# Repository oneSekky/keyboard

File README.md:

# keyboard
Custom keyboard for a couch TV setup. Screen build into the board, custom buttons, dials, and a trackball mouse.

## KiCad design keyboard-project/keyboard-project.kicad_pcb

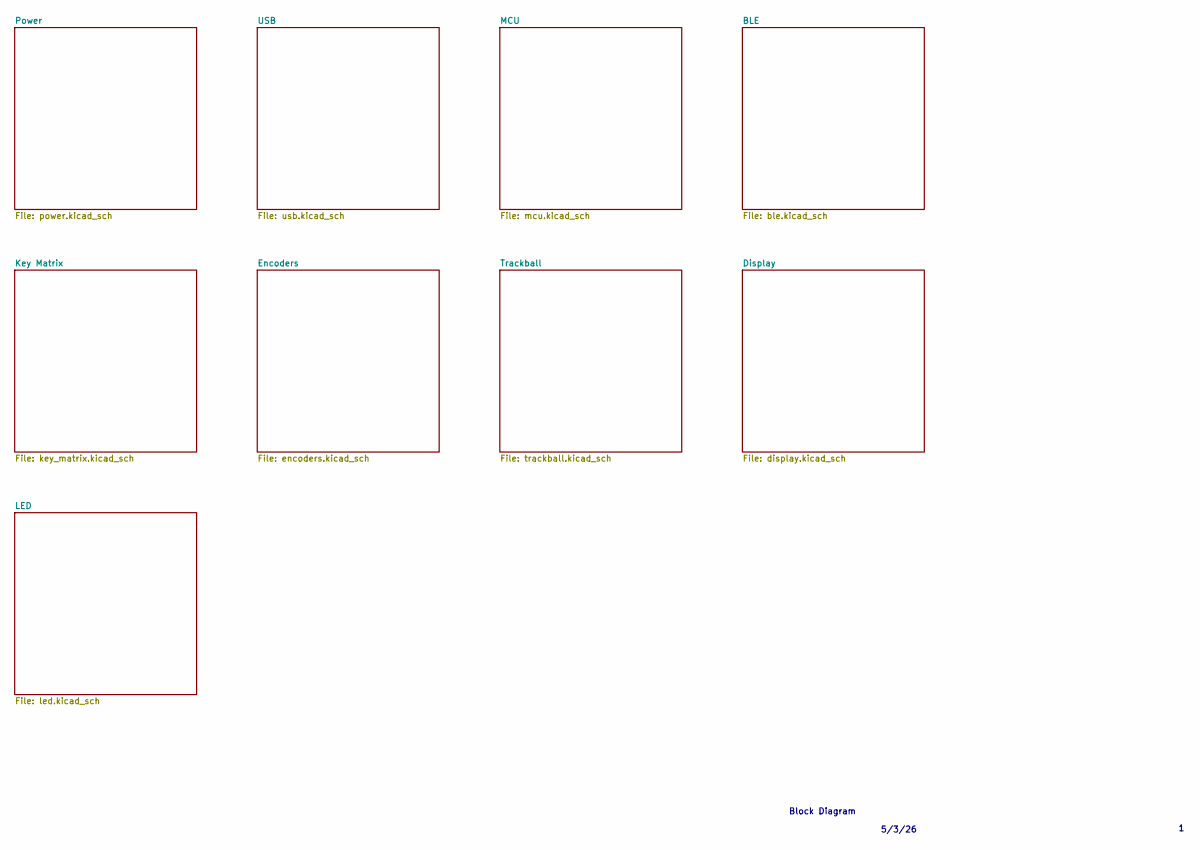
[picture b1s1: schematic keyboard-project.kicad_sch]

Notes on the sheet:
5/3/26
Block Diagram

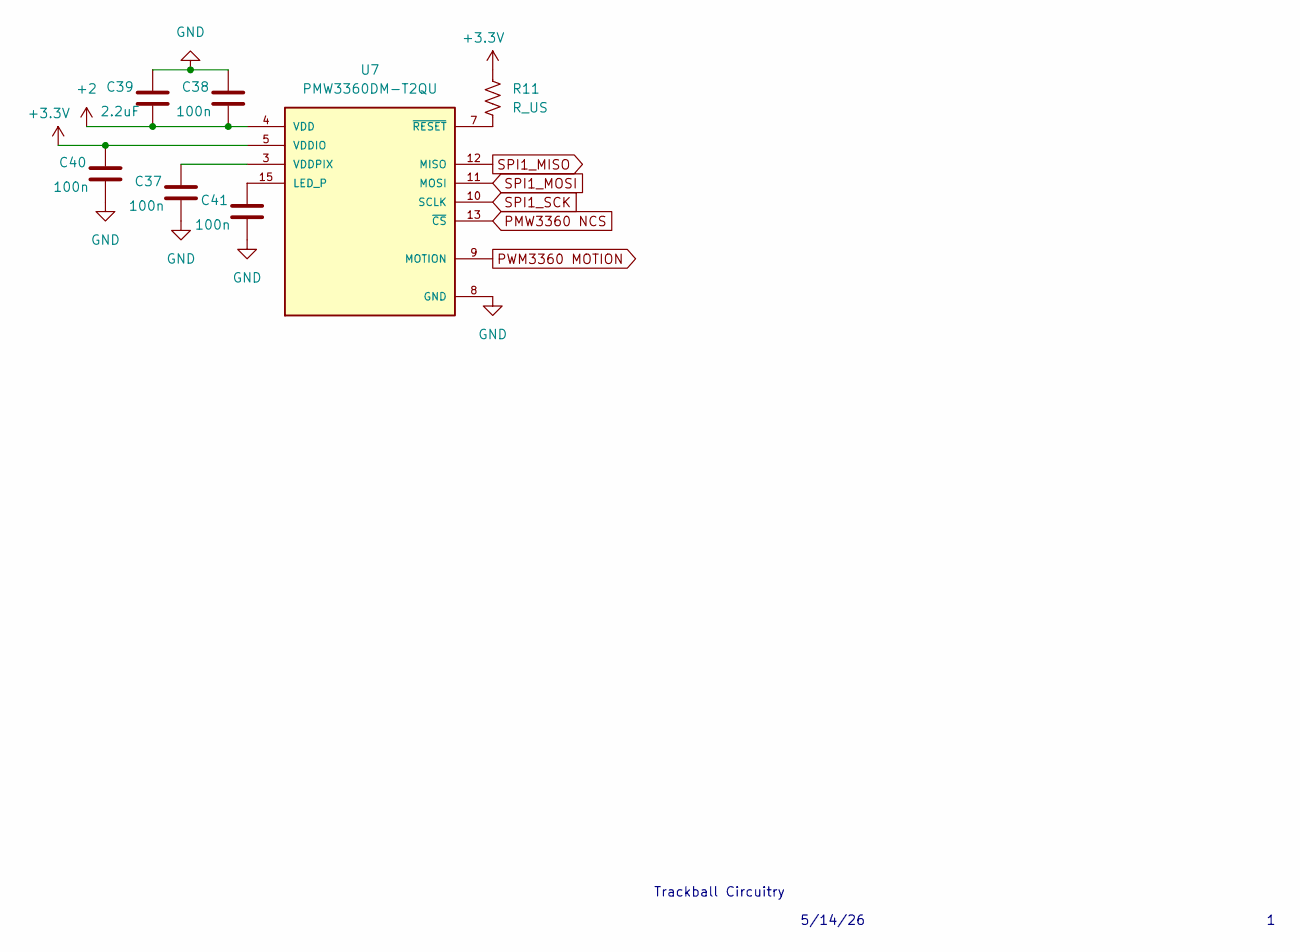
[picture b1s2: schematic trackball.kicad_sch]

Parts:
C37, C38, C40, C41: 100n; C_1206_3216Metric_Pad1.33x1.80mm_HandSolder
C39: 2.2uF; C_1206_3216Metric_Pad1.33x1.80mm_HandSolder
R11: R_US; R_1206_3216Metric_Pad1.30x1.75mm_HandSolder
U7: PMW3360DM-T2QU; PMW3360; MANUFACTURER_PART_NUMBER PMW3360DM-T2QU

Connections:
+2: C38.2, C39.2, U7.4 (VDD); also elsewhere on the board
+3.3V: C40.1, R11.1, U7.5 (VDDIO); also elsewhere on the board
GND: C37.2, C38.1, C39.1, C40.2, C41.2, U7.8 (GND); also elsewhere on the board
unnamed: C41.1, U7.15 (LED_P)
unnamed: C37.1, U7.3 (VDDPIX)
unnamed: R11.2, U7.7 (~RESET)
PMW3360 NCS: U7.13 (~CS); also elsewhere on the board
PWM3360 MOTION: U7.9 (MOTION); also elsewhere on the board
SPI1_MISO: U7.12 (MISO); also elsewhere on the board
SPI1_MOSI: U7.11 (MOSI); also elsewhere on the board
SPI1_SCK: U7.10 (SCLK); also elsewhere on the board

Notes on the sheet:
5/14/26
Trackball Circuitry

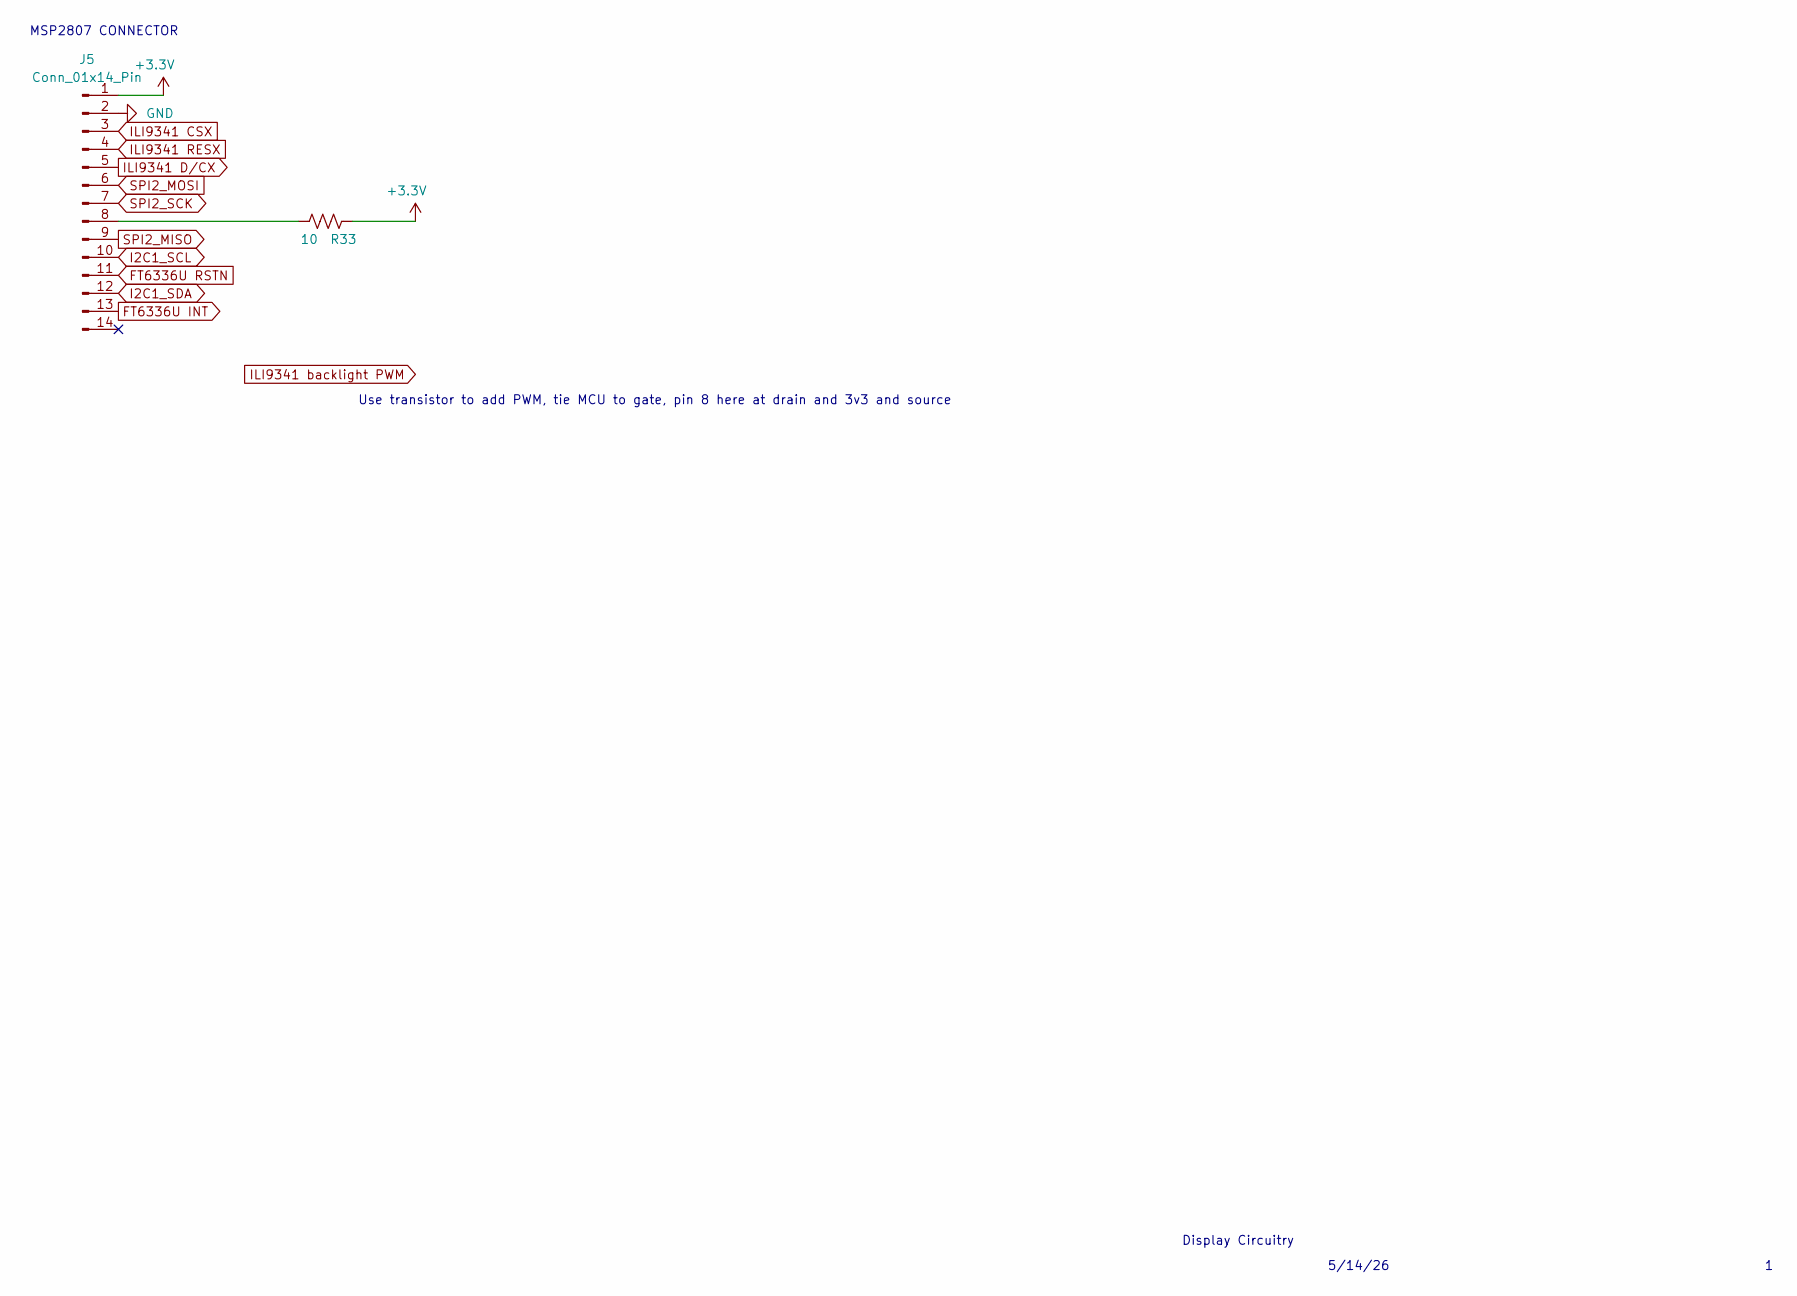
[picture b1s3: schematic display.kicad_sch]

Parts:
J5: Conn_01x14_Pin; PinHeader_1x14_P1.00mm_Vertical
R33: 10; R_1206_3216Metric_Pad1.30x1.75mm_HandSolder

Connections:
+3.3V: J5.1, R33.2; also elsewhere on the board
FT6336U INT: J5.13; also elsewhere on the board
FT6336U RSTN: J5.11; also elsewhere on the board
GND: J5.2; also elsewhere on the board
I2C1_SCL: J5.10; also elsewhere on the board
I2C1_SDA: J5.12; also elsewhere on the board
ILI9341 CSX: J5.3; also elsewhere on the board
ILI9341 D/CX: J5.5; also elsewhere on the board
ILI9341 RESX: J5.4; also elsewhere on the board
unnamed: J5.8, R33.1
SPI2_MISO: J5.9; also elsewhere on the board
SPI2_MOSI: J5.6; also elsewhere on the board
SPI2_SCK: J5.7; also elsewhere on the board

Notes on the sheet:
Display Circuitry
MSP2807 CONNECTOR
Use transistor to add PWM, tie MCU to gate, pin 8 here at drain and 3v3 and source
5/14/26

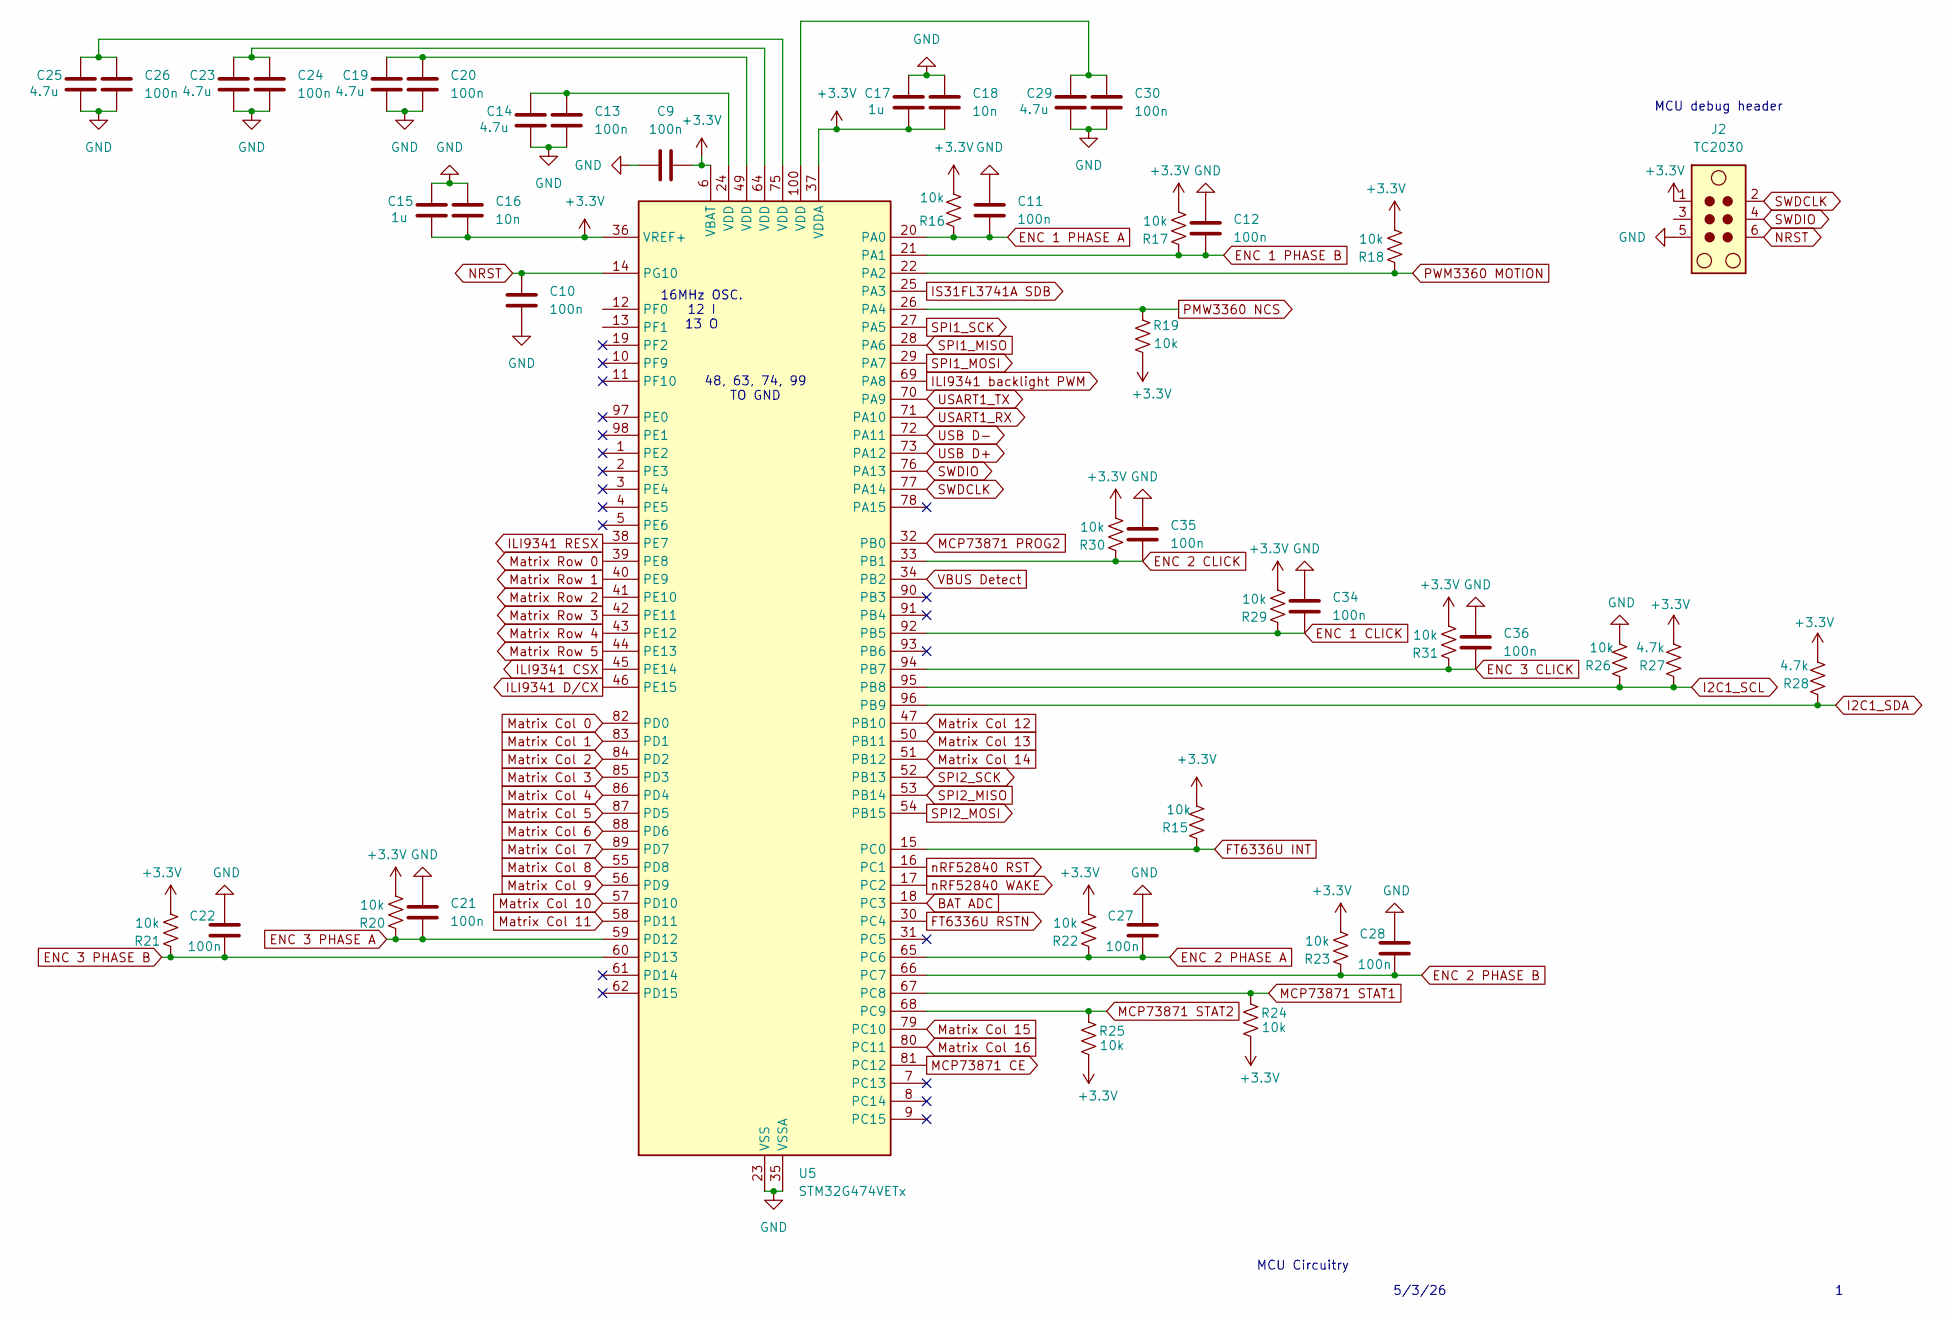
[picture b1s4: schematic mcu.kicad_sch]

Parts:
C9, C10, C11, C12, C13, C20, C21, C22, C24, C26, C27, C28, C30, C34, C35, C36: 100n; C_1206_3216Metric_Pad1.33x1.80mm_HandSolder
C14, C19, C23, C25, C29: 4.7u; C_1206_3216Metric_Pad1.33x1.80mm_HandSolder
C15, C17: 1u; C_1206_3216Metric_Pad1.33x1.80mm_HandSolder
C16, C18: 10n; C_1206_3216Metric_Pad1.33x1.80mm_HandSolder
J2: TC2030; Tag-Connect_TC2030-IDC-NL_2x03_P1.27mm_Vertical
R15, R16, R17, R18, R19, R20, R21, R22, R23, R24, R25, R26, R29, R30, R31: 10k; R_1206_3216Metric_Pad1.30x1.75mm_HandSolder
R27, R28: 4.7k; R_1206_3216Metric_Pad1.30x1.75mm_HandSolder
U5: STM32G474VETx; LQFP-100_14x14mm_P0.5mm

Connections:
+3.3V: C9.2, C15.2, C16.1, C17.2, C18.1, J2.1, R15.2, R16.2, R17.2, R18.2, R19.2, R20.2, R21.2, R22.2, R23.2, R24.2, R25.2, R27.2, R28.2, R29.2, R30.2, R31.2, U5.6 (VBAT), U5.36 (VREF+), U5.37 (VDDA); also elsewhere on the board
BAT ADC: U5.18 (PC3); also elsewhere on the board
ENC 1 CLICK: C34.1, R29.1, U5.92 (PB5); also elsewhere on the board
ENC 1 PHASE A: C11.1, R16.1, U5.20 (PA0); also elsewhere on the board
ENC 1 PHASE B: C12.1, R17.1, U5.21 (PA1); also elsewhere on the board
ENC 2 CLICK: C35.1, R30.1, U5.33 (PB1); also elsewhere on the board
ENC 2 PHASE A: C27.1, R22.1, U5.65 (PC6); also elsewhere on the board
ENC 2 PHASE B: C28.1, R23.1, U5.66 (PC7); also elsewhere on the board
ENC 3 CLICK: C36.1, R31.1, U5.94 (PB7); also elsewhere on the board
ENC 3 PHASE A: C21.1, R20.1, U5.59 (PD12); also elsewhere on the board
ENC 3 PHASE B: C22.1, R21.1, U5.60 (PD13); also elsewhere on the board
FT6336U INT: R15.1, U5.15 (PC0); also elsewhere on the board
FT6336U RSTN: U5.30 (PC4); also elsewhere on the board
GND: C9.1, C10.1, C11.2, C12.2, C13.1, C14.2, C15.1, C16.2, C17.1, C18.2, C19.2, C20.1, C21.2, C22.2, C23.2, C24.1, C25.2, C26.1, C27.2, C28.2, C29.2, C30.1, C34.2, C35.2, C36.2, J2.5, R26.2, U5.23 (VSS), U5.35 (VSSA), U5.48 (VSS), U5.63 (VSS), U5.74 (VSS), U5.99 (VSS); also elsewhere on the board
I2C1_SCL: R26.1, R27.1, U5.95 (PB8); also elsewhere on the board
I2C1_SDA: R28.1, U5.96 (PB9); also elsewhere on the board
ILI9341 CSX: U5.45 (PE14); also elsewhere on the board
ILI9341 D/CX: U5.46 (PE15); also elsewhere on the board
ILI9341 RESX: U5.38 (PE7); also elsewhere on the board
ILI9341 backlight PWM: U5.69 (PA8)
IS31FL3741A SDB: U5.25 (PA3); also elsewhere on the board
MCP73871 CE: U5.81 (PC12); also elsewhere on the board
MCP73871 PROG2: U5.32 (PB0); also elsewhere on the board
MCP73871 STAT1: R24.1, U5.67 (PC8); also elsewhere on the board
MCP73871 STAT2: R25.1, U5.68 (PC9); also elsewhere on the board
Matrix Col 0: U5.82 (PD0); also elsewhere on the board
Matrix Col 1: U5.83 (PD1); also elsewhere on the board
Matrix Col 2: U5.84 (PD2); also elsewhere on the board
Matrix Col 3: U5.85 (PD3); also elsewhere on the board
Matrix Col 4: U5.86 (PD4); also elsewhere on the board
Matrix Col 5: U5.87 (PD5); also elsewhere on the board
Matrix Col 6: U5.88 (PD6); also elsewhere on the board
Matrix Col 7: U5.89 (PD7); also elsewhere on the board
Matrix Col 8: U5.55 (PD8); also elsewhere on the board
Matrix Col 9: U5.56 (PD9); also elsewhere on the board
Matrix Col 10: U5.57 (PD10); also elsewhere on the board
Matrix Col 11: U5.58 (PD11); also elsewhere on the board
Matrix Col 12: U5.47 (PB10); also elsewhere on the board
Matrix Col 13: U5.50 (PB11); also elsewhere on the board
Matrix Col 14: U5.51 (PB12); also elsewhere on the board
Matrix Col 15: U5.79 (PC10); also elsewhere on the board
Matrix Col 16: U5.80 (PC11); also elsewhere on the board
Matrix Row 0: U5.39 (PE8); also elsewhere on the board
Matrix Row 1: U5.40 (PE9); also elsewhere on the board
Matrix Row 2: U5.41 (PE10); also elsewhere on the board
Matrix Row 3: U5.42 (PE11); also elsewhere on the board
Matrix Row 4: U5.43 (PE12); also elsewhere on the board
Matrix Row 5: U5.44 (PE13); also elsewhere on the board
NRST: C10.2, J2.6, U5.14 (PG10)
unnamed: C13.2, C14.1, U5.24 (VDD)
unnamed: C19.1, C20.2, U5.49 (VDD)
unnamed: C23.1, C24.2, U5.64 (VDD)
unnamed: C25.1, C26.2, U5.75 (VDD)
unnamed: C29.1, C30.2, U5.100 (VDD)
PMW3360 NCS: R19.1, U5.26 (PA4); also elsewhere on the board
PWM3360 MOTION: R18.1, U5.22 (PA2); also elsewhere on the board
SPI1_MISO: U5.28 (PA6); also elsewhere on the board
SPI1_MOSI: U5.29 (PA7); also elsewhere on the board
SPI1_SCK: U5.27 (PA5); also elsewhere on the board
SPI2_MISO: U5.53 (PB14); also elsewhere on the board
SPI2_MOSI: U5.54 (PB15); also elsewhere on the board
SPI2_SCK: U5.52 (PB13); also elsewhere on the board
SWDCLK: J2.2, U5.77 (PA14)
SWDIO: J2.4, U5.76 (PA13)
USART1_RX: U5.71 (PA10); also elsewhere on the board
USART1_TX: U5.70 (PA9); also elsewhere on the board
USB D+: U5.73 (PA12); also elsewhere on the board
USB D-: U5.72 (PA11); also elsewhere on the board
VBUS Detect: U5.34 (PB2); also elsewhere on the board
nRF52840 RST: U5.16 (PC1); also elsewhere on the board
nRF52840 WAKE: U5.17 (PC2); also elsewhere on the board

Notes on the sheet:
MCU Circuitry
MCU debug header
48, 63, 74, 99 TO GND
16MHz OSC. 12 I 13 O
5/3/26

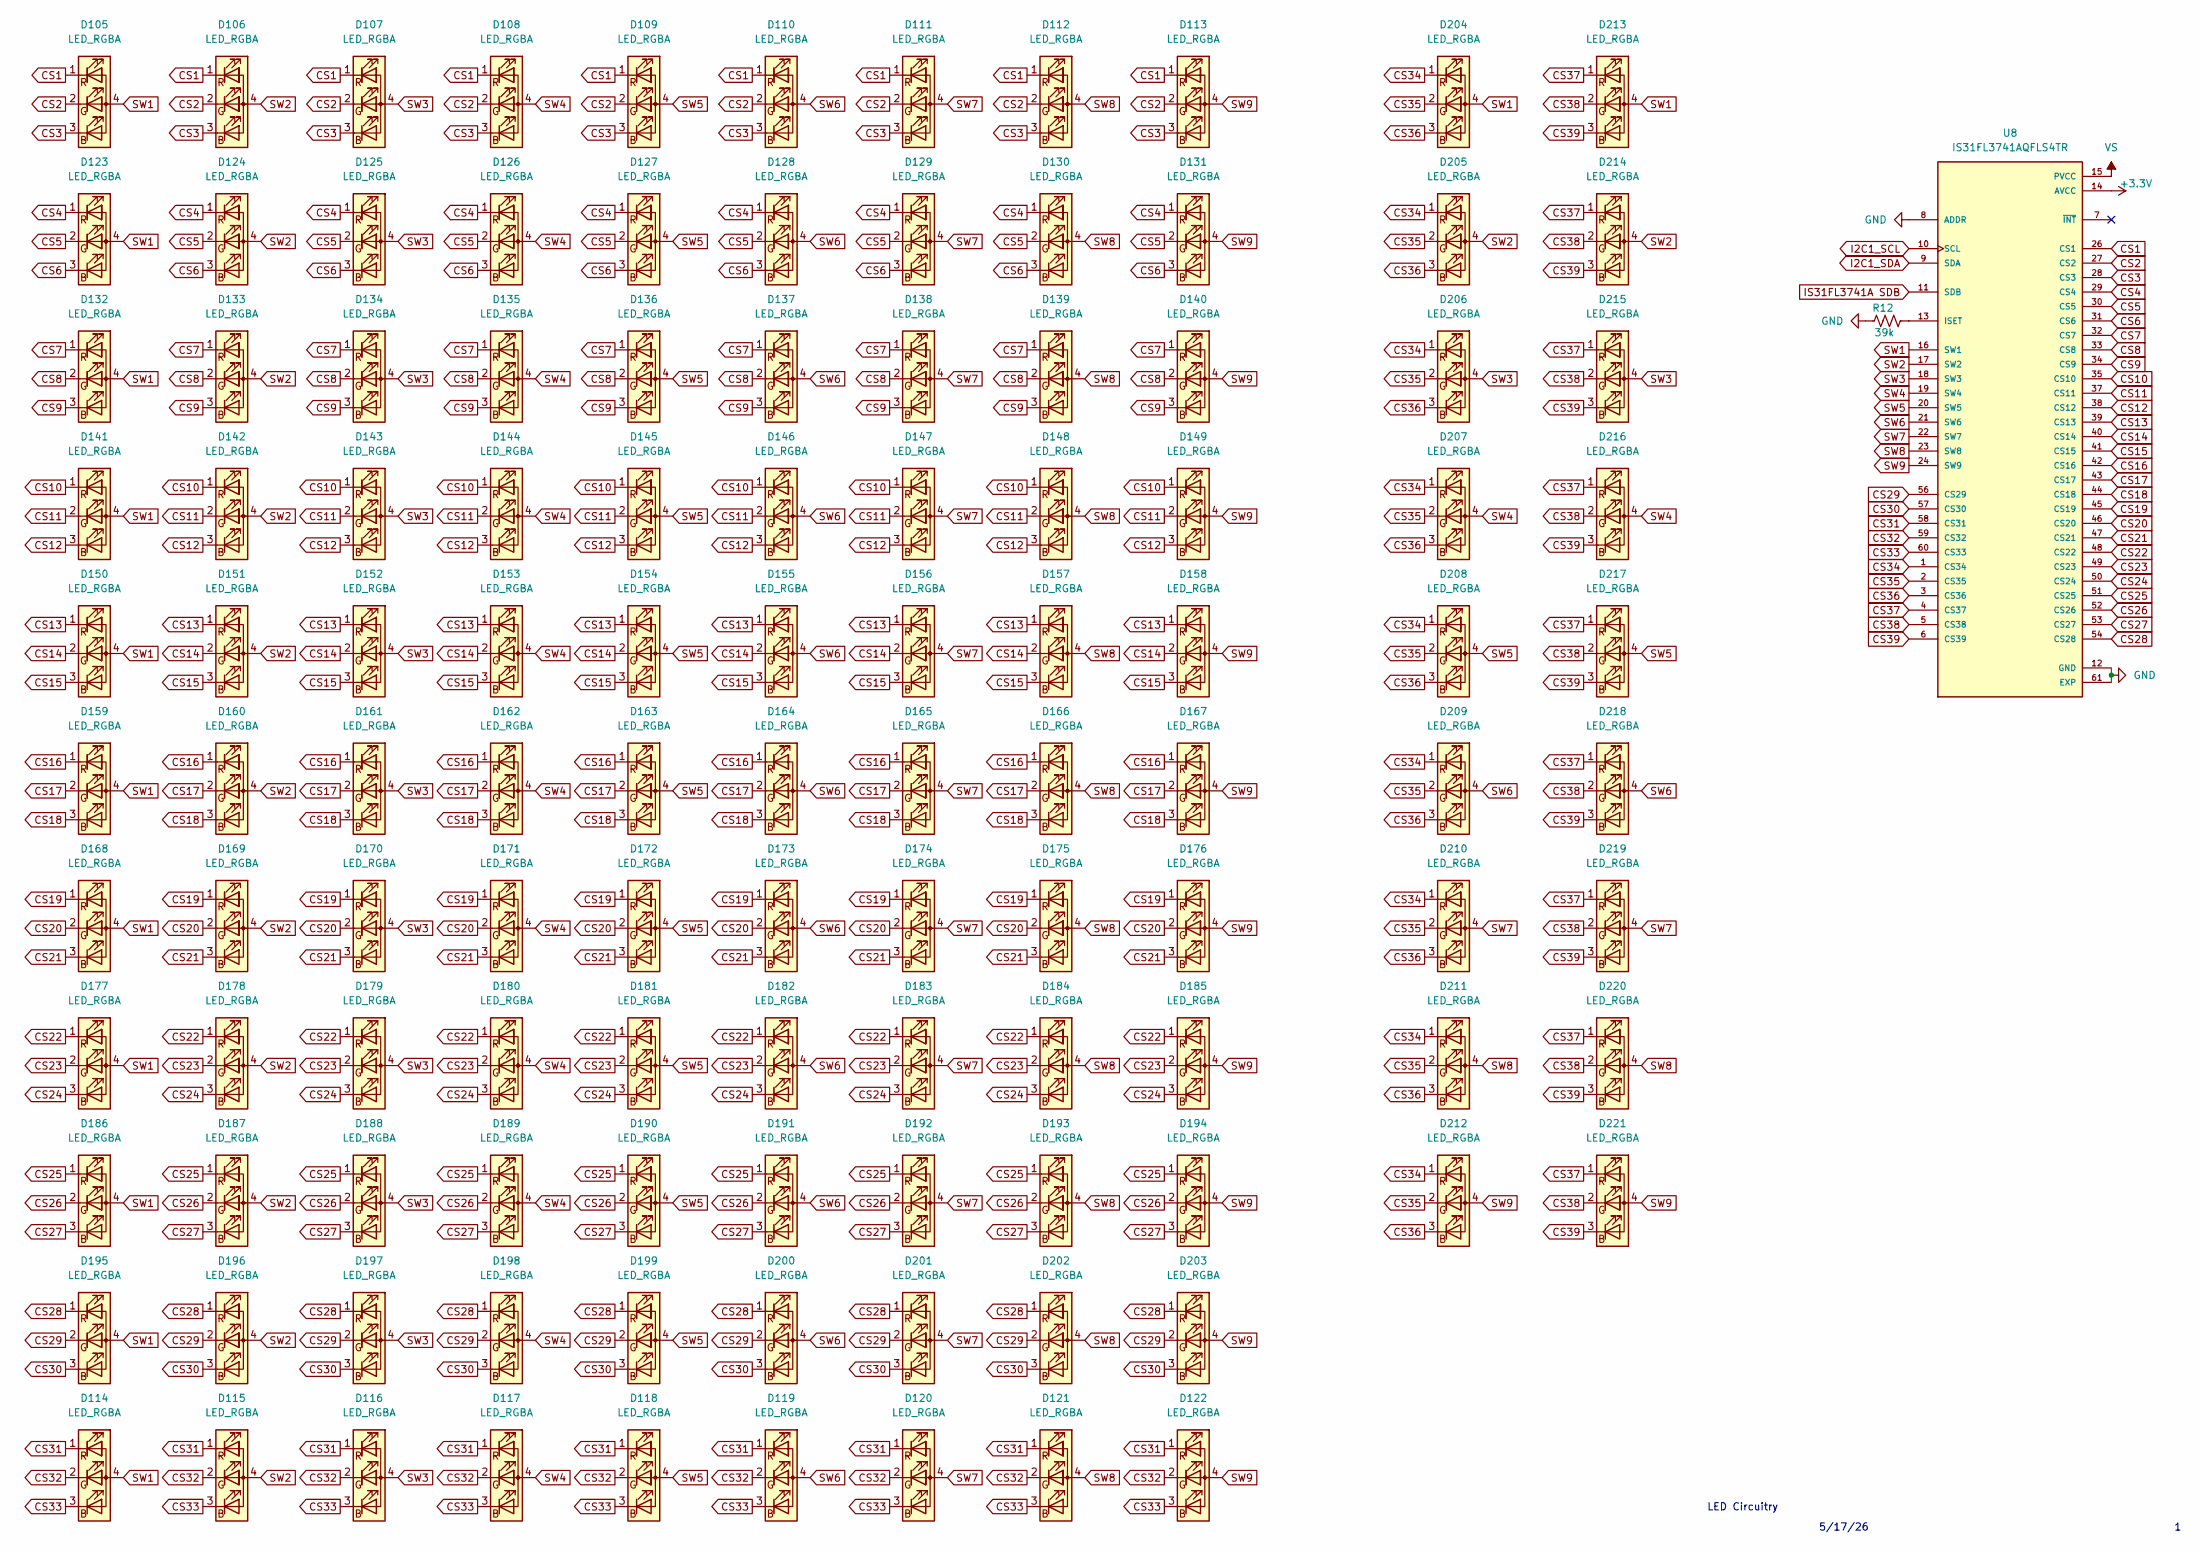
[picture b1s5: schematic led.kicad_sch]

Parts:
D105, D106, D107, D108, D109, D110, D111, D112, D113, D114, D115, D116, D117, D118, D119, D120, D121, D122, D123, D124, D125, D126, D127, D128, D129, D130, D131, D132, D133, D134, D135, D136, D137, D138, D139, D140, D141, D142, D143, D144, D145, D146, D147, D148, D149, D150, D151, D152, D153, D154, D155, D156, D157, D158, D159, D160, D161, D162, D163, D164, D165, D166, D167, D168, D169, D170, D171, D172, D173, D174, D175, D176, D177, D178, D179, D180, D181, D182, D183, D184, D185, D186, D187, D188, D189, D190, D191, D192, D193, D194, D195, D196, D197, D198, D199, D200, D201, D202, D203, D204, D205, D206, D207, D208, D209, D210, D211, D212, D213, D214, D215, D216, D217, D218, D219, D220, D221: LED_RGBA; LED_AAA3528LSEKJ3ZGKQBKS
R12: 39k; R_1206_3216Metric_Pad1.30x1.75mm_HandSolder
U8: IS31FL3741AQFLS4TR; TQFP-48-1EP_7x7mm_P0.5mm_EP4.11x4.11mm; PARTREV C

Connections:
+3.3V: U8.14 (AVCC); also elsewhere on the board
CHARGER OUT / REGULATOR IN: U8.15 (PVCC), U8.25 (PVCC); also elsewhere on the board
CS1: D105.1 (RK), D106.1 (RK), D107.1 (RK), D108.1 (RK), D109.1 (RK), D110.1 (RK), D111.1 (RK), D112.1 (RK), D113.1 (RK), U8.26 (CS1)
CS2: D105.2 (GK), D106.2 (GK), D107.2 (GK), D108.2 (GK), D109.2 (GK), D110.2 (GK), D111.2 (GK), D112.2 (GK), D113.2 (GK), U8.27 (CS2)
CS3: D105.3 (BK), D106.3 (BK), D107.3 (BK), D108.3 (BK), D109.3 (BK), D110.3 (BK), D111.3 (BK), D112.3 (BK), D113.3 (BK), U8.28 (CS3)
CS4: D123.1 (RK), D124.1 (RK), D125.1 (RK), D126.1 (RK), D127.1 (RK), D128.1 (RK), D129.1 (RK), D130.1 (RK), D131.1 (RK), U8.29 (CS4)
CS5: D123.2 (GK), D124.2 (GK), D125.2 (GK), D126.2 (GK), D127.2 (GK), D128.2 (GK), D129.2 (GK), D130.2 (GK), D131.2 (GK), U8.30 (CS5)
CS6: D123.3 (BK), D124.3 (BK), D125.3 (BK), D126.3 (BK), D127.3 (BK), D128.3 (BK), D129.3 (BK), D130.3 (BK), D131.3 (BK), U8.31 (CS6)
CS7: D132.1 (RK), D133.1 (RK), D134.1 (RK), D135.1 (RK), D136.1 (RK), D137.1 (RK), D138.1 (RK), D139.1 (RK), D140.1 (RK), U8.32 (CS7)
CS8: D132.2 (GK), D133.2 (GK), D134.2 (GK), D135.2 (GK), D136.2 (GK), D137.2 (GK), D138.2 (GK), D139.2 (GK), D140.2 (GK), U8.33 (CS8)
CS9: D132.3 (BK), D133.3 (BK), D134.3 (BK), D135.3 (BK), D136.3 (BK), D137.3 (BK), D138.3 (BK), D139.3 (BK), D140.3 (BK), U8.34 (CS9)
CS10: D141.1 (RK), D142.1 (RK), D143.1 (RK), D144.1 (RK), D145.1 (RK), D146.1 (RK), D147.1 (RK), D148.1 (RK), D149.1 (RK), U8.35 (CS10)
CS11: D141.2 (GK), D142.2 (GK), D143.2 (GK), D144.2 (GK), D145.2 (GK), D146.2 (GK), D147.2 (GK), D148.2 (GK), D149.2 (GK), U8.37 (CS11)
CS12: D141.3 (BK), D142.3 (BK), D143.3 (BK), D144.3 (BK), D145.3 (BK), D146.3 (BK), D147.3 (BK), D148.3 (BK), D149.3 (BK), U8.38 (CS12)
CS13: D150.1 (RK), D151.1 (RK), D152.1 (RK), D153.1 (RK), D154.1 (RK), D155.1 (RK), D156.1 (RK), D157.1 (RK), D158.1 (RK), U8.39 (CS13)
CS14: D150.2 (GK), D151.2 (GK), D152.2 (GK), D153.2 (GK), D154.2 (GK), D155.2 (GK), D156.2 (GK), D157.2 (GK), D158.2 (GK), U8.40 (CS14)
CS15: D150.3 (BK), D151.3 (BK), D152.3 (BK), D153.3 (BK), D154.3 (BK), D155.3 (BK), D156.3 (BK), D157.3 (BK), D158.3 (BK), U8.41 (CS15)
CS16: D159.1 (RK), D160.1 (RK), D161.1 (RK), D162.1 (RK), D163.1 (RK), D164.1 (RK), D165.1 (RK), D166.1 (RK), D167.1 (RK), U8.42 (CS16)
CS17: D159.2 (GK), D160.2 (GK), D161.2 (GK), D162.2 (GK), D163.2 (GK), D164.2 (GK), D165.2 (GK), D166.2 (GK), D167.2 (GK), U8.43 (CS17)
CS18: D159.3 (BK), D160.3 (BK), D161.3 (BK), D162.3 (BK), D163.3 (BK), D164.3 (BK), D165.3 (BK), D166.3 (BK), D167.3 (BK), U8.44 (CS18)
CS19: D168.1 (RK), D169.1 (RK), D170.1 (RK), D171.1 (RK), D172.1 (RK), D173.1 (RK), D174.1 (RK), D175.1 (RK), D176.1 (RK), U8.45 (CS19)
CS20: D168.2 (GK), D169.2 (GK), D170.2 (GK), D171.2 (GK), D172.2 (GK), D173.2 (GK), D174.2 (GK), D175.2 (GK), D176.2 (GK), U8.46 (CS20)
CS21: D168.3 (BK), D169.3 (BK), D170.3 (BK), D171.3 (BK), D172.3 (BK), D173.3 (BK), D174.3 (BK), D175.3 (BK), D176.3 (BK), U8.47 (CS21)
CS22: D177.1 (RK), D178.1 (RK), D179.1 (RK), D180.1 (RK), D181.1 (RK), D182.1 (RK), D183.1 (RK), D184.1 (RK), D185.1 (RK), U8.48 (CS22)
CS23: D177.2 (GK), D178.2 (GK), D179.2 (GK), D180.2 (GK), D181.2 (GK), D182.2 (GK), D183.2 (GK), D184.2 (GK), D185.2 (GK), U8.49 (CS23)
CS24: D177.3 (BK), D178.3 (BK), D179.3 (BK), D180.3 (BK), D181.3 (BK), D182.3 (BK), D183.3 (BK), D184.3 (BK), D185.3 (BK), U8.50 (CS24)
CS25: D186.1 (RK), D187.1 (RK), D188.1 (RK), D189.1 (RK), D190.1 (RK), D191.1 (RK), D192.1 (RK), D193.1 (RK), D194.1 (RK), U8.51 (CS25)
CS26: D186.2 (GK), D187.2 (GK), D188.2 (GK), D189.2 (GK), D190.2 (GK), D191.2 (GK), D192.2 (GK), D193.2 (GK), D194.2 (GK), U8.52 (CS26)
CS27: D186.3 (BK), D187.3 (BK), D188.3 (BK), D189.3 (BK), D190.3 (BK), D191.3 (BK), D192.3 (BK), D193.3 (BK), D194.3 (BK), U8.53 (CS27)
CS28: D195.1 (RK), D196.1 (RK), D197.1 (RK), D198.1 (RK), D199.1 (RK), D200.1 (RK), D201.1 (RK), D202.1 (RK), D203.1 (RK), U8.54 (CS28)
CS29: D195.2 (GK), D196.2 (GK), D197.2 (GK), D198.2 (GK), D199.2 (GK), D200.2 (GK), D201.2 (GK), D202.2 (GK), D203.2 (GK), U8.56 (CS29)
CS30: D195.3 (BK), D196.3 (BK), D197.3 (BK), D198.3 (BK), D199.3 (BK), D200.3 (BK), D201.3 (BK), D202.3 (BK), D203.3 (BK), U8.57 (CS30)
CS31: D114.1 (RK), D115.1 (RK), D116.1 (RK), D117.1 (RK), D118.1 (RK), D119.1 (RK), D120.1 (RK), D121.1 (RK), D122.1 (RK), U8.58 (CS31)
CS32: D114.2 (GK), D115.2 (GK), D116.2 (GK), D117.2 (GK), D118.2 (GK), D119.2 (GK), D120.2 (GK), D121.2 (GK), D122.2 (GK), U8.59 (CS32)
CS33: D114.3 (BK), D115.3 (BK), D116.3 (BK), D117.3 (BK), D118.3 (BK), D119.3 (BK), D120.3 (BK), D121.3 (BK), D122.3 (BK), U8.60 (CS33)
CS34: D204.1 (RK), D205.1 (RK), D206.1 (RK), D207.1 (RK), D208.1 (RK), D209.1 (RK), D210.1 (RK), D211.1 (RK), D212.1 (RK), U8.1 (CS34)
CS35: D204.2 (GK), D205.2 (GK), D206.2 (GK), D207.2 (GK), D208.2 (GK), D209.2 (GK), D210.2 (GK), D211.2 (GK), D212.2 (GK), U8.2 (CS35)
CS36: D204.3 (BK), D205.3 (BK), D206.3 (BK), D207.3 (BK), D208.3 (BK), D209.3 (BK), D210.3 (BK), D211.3 (BK), D212.3 (BK), U8.3 (CS36)
CS37: D213.1 (RK), D214.1 (RK), D215.1 (RK), D216.1 (RK), D217.1 (RK), D218.1 (RK), D219.1 (RK), D220.1 (RK), D221.1 (RK), U8.4 (CS37)
CS38: D213.2 (GK), D214.2 (GK), D215.2 (GK), D216.2 (GK), D217.2 (GK), D218.2 (GK), D219.2 (GK), D220.2 (GK), D221.2 (GK), U8.5 (CS38)
CS39: D213.3 (BK), D214.3 (BK), D215.3 (BK), D216.3 (BK), D217.3 (BK), D218.3 (BK), D219.3 (BK), D220.3 (BK), D221.3 (BK), U8.6 (CS39)
GND: R12.1, U8.8 (ADDR), U8.12 (GND), U8.36 (GND), U8.55 (GND), U8.61 (EXP); also elsewhere on the board
I2C1_SCL: U8.10 (SCL); also elsewhere on the board
I2C1_SDA: U8.9 (SDA); also elsewhere on the board
IS31FL3741A SDB: U8.11 (SDB); also elsewhere on the board
unnamed: R12.2, U8.13 (ISET)
SW1: D105.4 (A), D114.4 (A), D123.4 (A), D132.4 (A), D141.4 (A), D150.4 (A), D159.4 (A), D168.4 (A), D177.4 (A), D186.4 (A), D195.4 (A), D204.4 (A), D213.4 (A), U8.16 (SW1)
SW2: D106.4 (A), D115.4 (A), D124.4 (A), D133.4 (A), D142.4 (A), D151.4 (A), D160.4 (A), D169.4 (A), D178.4 (A), D187.4 (A), D196.4 (A), D205.4 (A), D214.4 (A), U8.17 (SW2)
SW3: D107.4 (A), D116.4 (A), D125.4 (A), D134.4 (A), D143.4 (A), D152.4 (A), D161.4 (A), D170.4 (A), D179.4 (A), D188.4 (A), D197.4 (A), D206.4 (A), D215.4 (A), U8.18 (SW3)
SW4: D108.4 (A), D117.4 (A), D126.4 (A), D135.4 (A), D144.4 (A), D153.4 (A), D162.4 (A), D171.4 (A), D180.4 (A), D189.4 (A), D198.4 (A), D207.4 (A), D216.4 (A), U8.19 (SW4)
SW5: D109.4 (A), D118.4 (A), D127.4 (A), D136.4 (A), D145.4 (A), D154.4 (A), D163.4 (A), D172.4 (A), D181.4 (A), D190.4 (A), D199.4 (A), D208.4 (A), D217.4 (A), U8.20 (SW5)
SW6: D110.4 (A), D119.4 (A), D128.4 (A), D137.4 (A), D146.4 (A), D155.4 (A), D164.4 (A), D173.4 (A), D182.4 (A), D191.4 (A), D200.4 (A), D209.4 (A), D218.4 (A), U8.21 (SW6)
SW7: D111.4 (A), D120.4 (A), D129.4 (A), D138.4 (A), D147.4 (A), D156.4 (A), D165.4 (A), D174.4 (A), D183.4 (A), D192.4 (A), D201.4 (A), D210.4 (A), D219.4 (A), U8.22 (SW7)
SW8: D112.4 (A), D121.4 (A), D130.4 (A), D139.4 (A), D148.4 (A), D157.4 (A), D166.4 (A), D175.4 (A), D184.4 (A), D193.4 (A), D202.4 (A), D211.4 (A), D220.4 (A), U8.23 (SW8)
SW9: D113.4 (A), D122.4 (A), D131.4 (A), D140.4 (A), D149.4 (A), D158.4 (A), D167.4 (A), D176.4 (A), D185.4 (A), D194.4 (A), D203.4 (A), D212.4 (A), D221.4 (A), U8.24 (SW9)

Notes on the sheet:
LED Circuitry
5/17/26

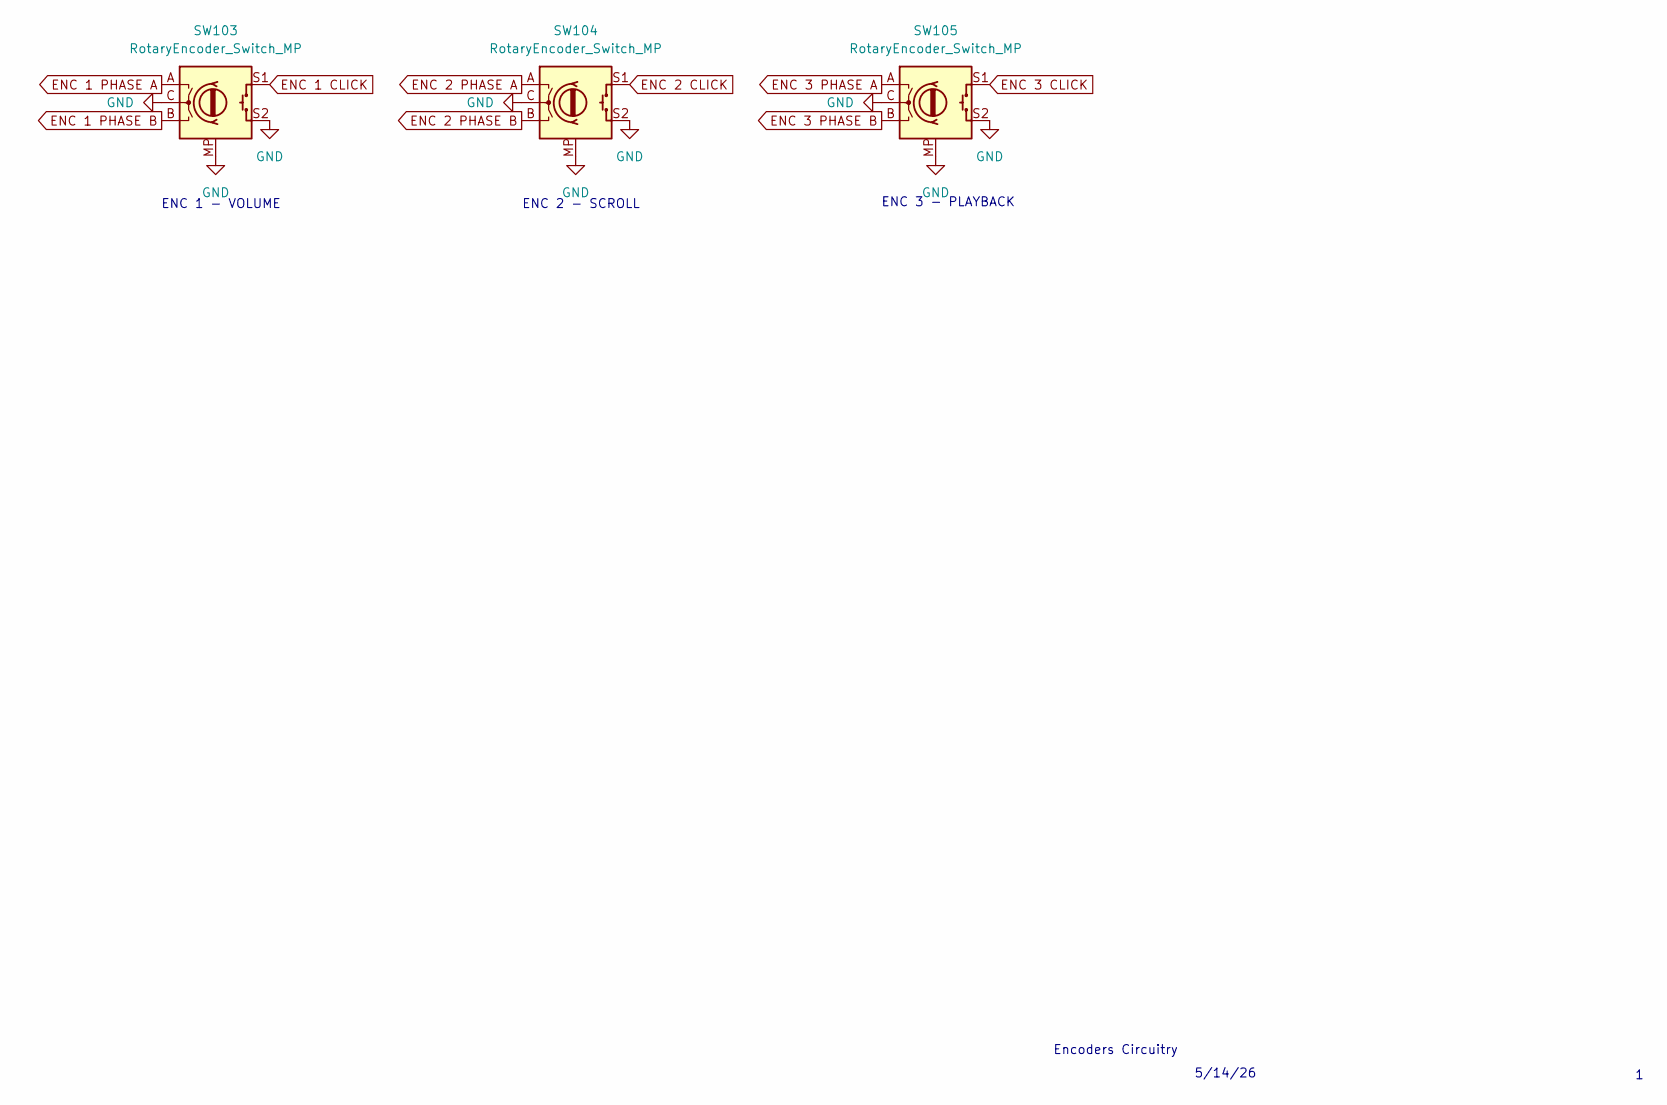
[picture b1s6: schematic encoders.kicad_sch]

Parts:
SW103, SW104, SW105: RotaryEncoder_Switch_MP; RotaryEncoder_Bourns_Horizontal_PEC12R-2x17F-Sxxxx

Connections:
ENC 1 CLICK: SW103.S1; also elsewhere on the board
ENC 1 PHASE A: SW103.A; also elsewhere on the board
ENC 1 PHASE B: SW103.B; also elsewhere on the board
ENC 2 CLICK: SW104.S1; also elsewhere on the board
ENC 2 PHASE A: SW104.A; also elsewhere on the board
ENC 2 PHASE B: SW104.B; also elsewhere on the board
ENC 3 CLICK: SW105.S1; also elsewhere on the board
ENC 3 PHASE A: SW105.A; also elsewhere on the board
ENC 3 PHASE B: SW105.B; also elsewhere on the board
GND: SW103.C, SW103.MP, SW103.S2, SW104.C, SW104.MP, SW104.S2, SW105.C, SW105.MP, SW105.S2; also elsewhere on the board

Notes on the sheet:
ENC 2 - SCROLL
5/14/26
ENC 1 - VOLUME
Encoders Circuitry
ENC 3 - PLAYBACK
